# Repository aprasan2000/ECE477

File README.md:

# Purdue ECE477
Senior Design<br />
"Noggin" Smart Hard Hat<br />
BY: Akshaj Prasannakumar, Ryan Domanski, Mooyeon Kim, and Dev Shah<br />
website: https://engineering.purdue.edu/477grp19/index.html<br />
Branch with Final code is Noggin-Final Branch<br />

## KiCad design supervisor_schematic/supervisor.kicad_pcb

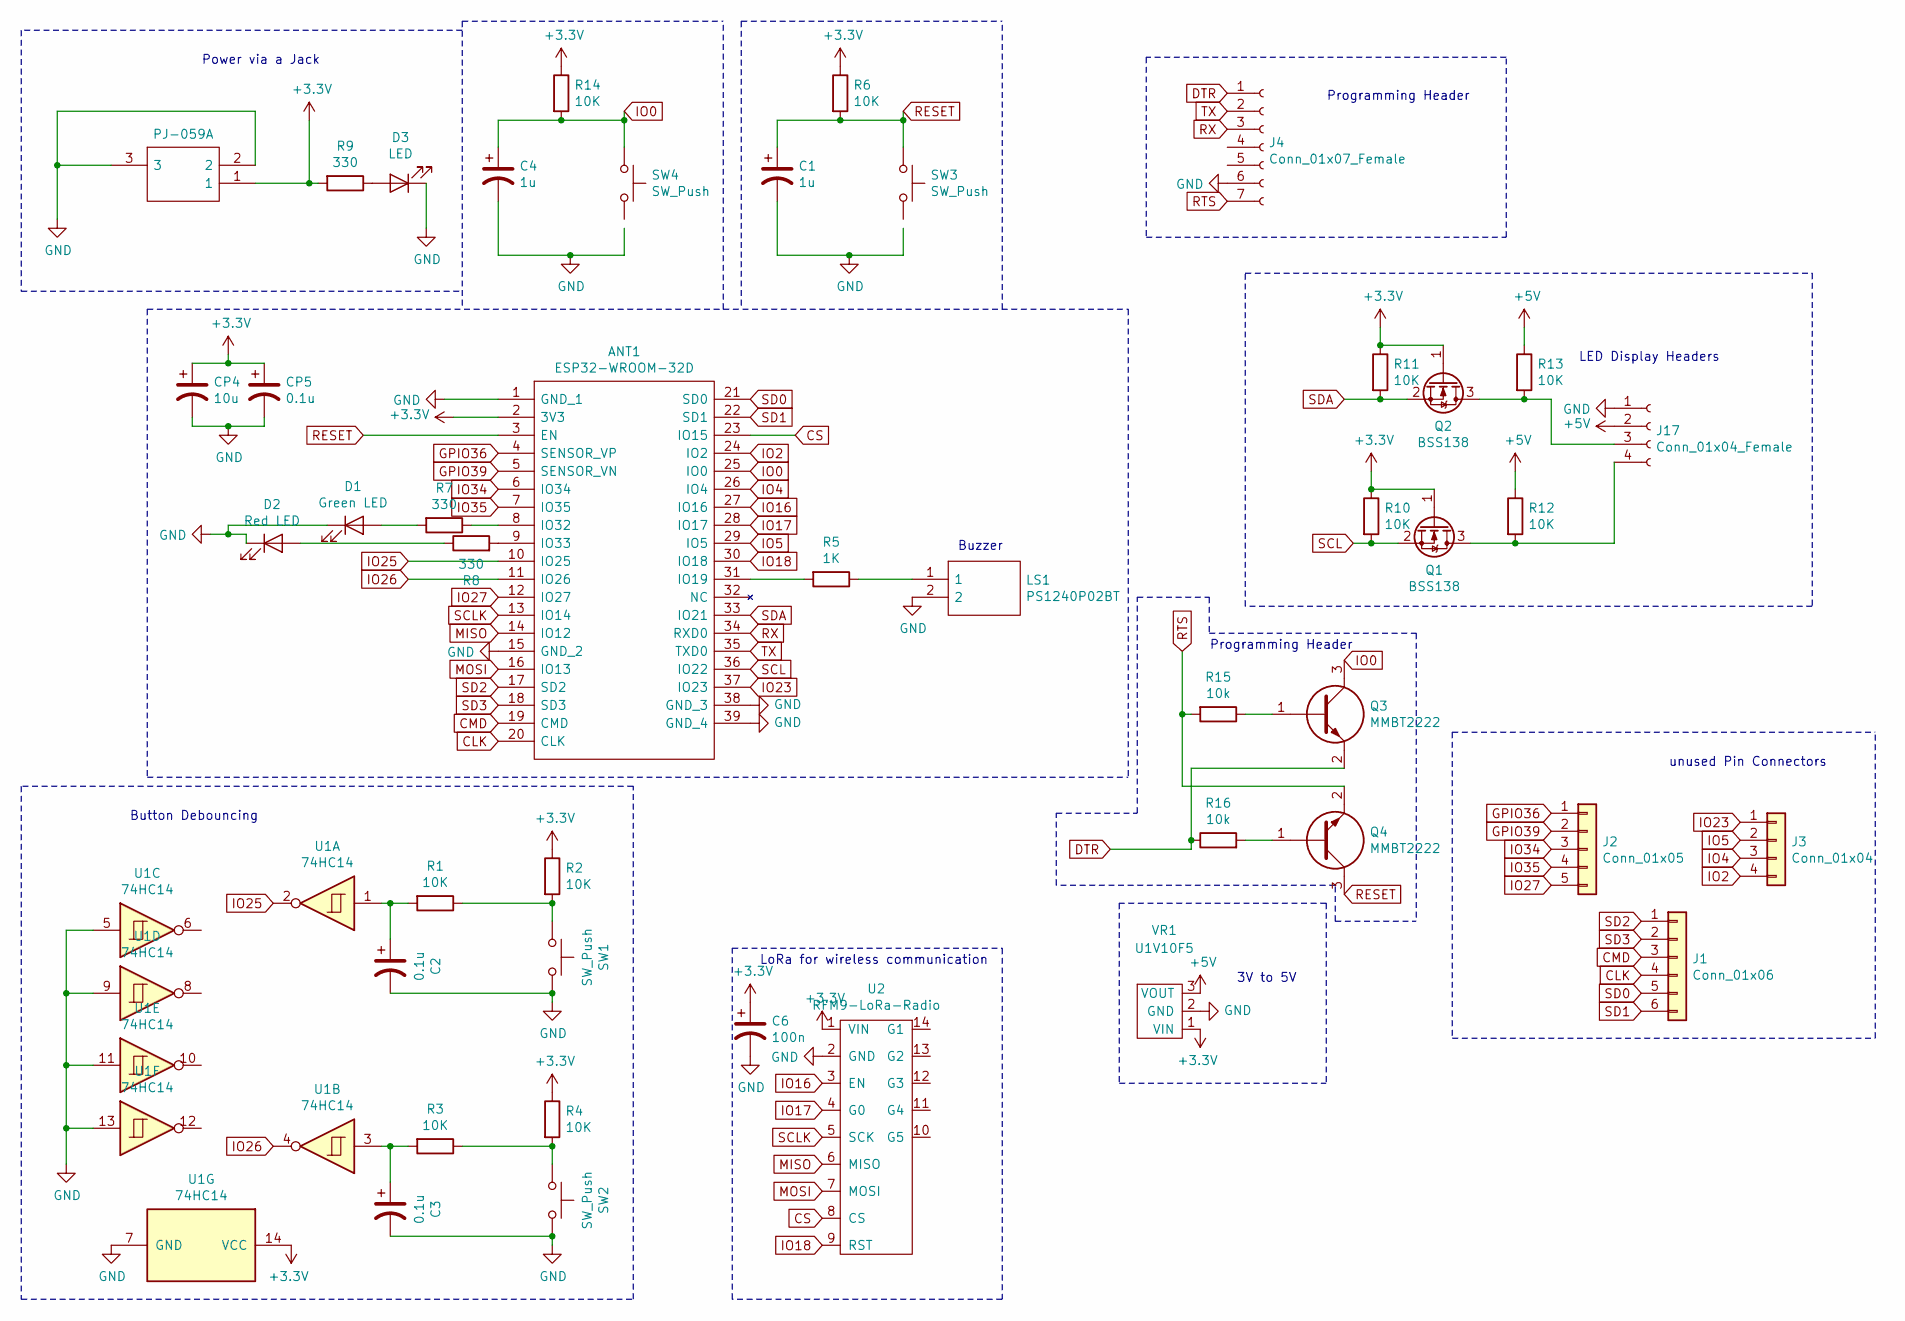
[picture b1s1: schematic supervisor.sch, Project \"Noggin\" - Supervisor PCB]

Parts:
ANT1: ESP32-WROOM-32D; ESP32WROOM32D; Manufacturer_Part_Number ESP32-WROOM-32D; Mouser Part Number N/A
C1, C4: 1u; C_0805_2012Metric_Pad1.15x1.40mm_HandSolder
C2, C3: 0.1u; C_0805_2012Metric_Pad1.15x1.40mm_HandSolder
C6: 100n; C_0805_2012Metric_Pad1.15x1.40mm_HandSolder
CP4: 10u; C_0805_2012Metric_Pad1.15x1.40mm_HandSolder
CP5: 0.1u; C_0805_2012Metric_Pad1.15x1.40mm_HandSolder
D1: Green LED; 0805_LED_Extended
D2: Red LED; 0805_LED_Extended
D3: LED; 0805_LED_Extended
J1: Conn_01x06; PinHeader_1x06_P2.54mm_Vertical
J2: Conn_01x05; PinHeader_1x05_P2.54mm_Vertical
J3: Conn_01x04; PinHeader_1x04_P2.54mm_Vertical
J4: Conn_01x07_Female; PinHeader_1x07_P2.54mm_Vertical
J17: Conn_01x04_Female; PinHeader_1x04_P2.54mm_Vertical
Jack1: PJ-059A; PJ059A; Manufacturer_Part_Number PJ-059A; Mouser Part Number 490-PJ-059A
LS1: PS1240P02BT; Manufacturer_Part_Number PS1240P02BT; Mouser Part Number 810-PS1240P02BT
Q1, Q2: BSS138; SOT-23
Q3, Q4: MMBT2222; SOT95P240X114-3N; Manufacturer_Part_Number MMBT2222; Mouser Part Number 512-MMBT2222
R1, R2, R3, R4, R6, R10, R11, R12, R13, R14: 10K; R_0805_2012Metric_Pad1.15x1.40mm_HandSolder
R5: 1K; R_0805_2012Metric_Pad1.15x1.40mm_HandSolder
R7, R8, R9: 330; R_0805_2012Metric_Pad1.15x1.40mm_HandSolder
R15, R16: 10k; R_0805_2012Metric_Pad1.15x1.40mm_HandSolder
SW1, SW2, SW3, SW4: SW_Push; SW_PUSH_6mm
U1: 74HC14; DIP-14_W7.62mm
U2: RFM9-LoRa-Radio; RFM9x
VR1: U1V10F5; U1V10F5-VR

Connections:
+3V3: ANT1.2 (3V3), C6.1, CP4.1, CP5.1, Jack1.1, Q1.1 (G), Q2.1 (G), R2.1, R4.1, R6.1, R9.2, R10.1, R11.1, R14.1, U1.14 (VCC), U2.1 (VIN), VR1.1 (VIN)
+5V: J17.2, R12.1, R13.1, VR1.3 (VOUT)
CLK: ANT1.20 (CLK), J1.4
CMD: ANT1.19 (CMD), J1.3
CS: ANT1.23 (IO15), U2.8 (CS)
DTR: J4.1, Q3.2, R16.1
GND: ANT1.1 (GND_1), ANT1.15 (GND_2), ANT1.38 (GND_3), ANT1.39 (GND_4), C1.2, C2.2, C3.2, C4.2, C6.2, CP4.2, CP5.2, D1.1 (K), D2.1 (K), D3.1 (K), J4.6, J17.1, Jack1.2, Jack1.3, LS1.2, SW1.2, SW2.2, U1.5, U1.7 (GND), U1.9, U1.11, U1.13, U2.2 (GND), VR1.2 (GND)
GPIO36: ANT1.4 (SENSOR_VP), J2.1
GPIO39: ANT1.5 (SENSOR_VN), J2.2
IO0: ANT1.25 (IO0), C4.1, Q3.3, R14.2, SW4.1
IO2: ANT1.24 (IO2), J3.4
IO4: ANT1.26 (IO4), J3.3
IO5: ANT1.29 (IO5), J3.2
IO16: ANT1.27 (IO16), U2.3 (EN)
IO17: ANT1.28 (IO17), U2.4 (G0)
IO18: ANT1.30 (IO18), U2.9 (RST)
IO23: ANT1.37 (IO23), J3.1
IO25: ANT1.10 (IO25), U1.2
IO26: ANT1.11 (IO26), U1.4
IO27: ANT1.12 (IO27), J2.5
IO34: ANT1.6 (IO34), J2.3
IO35: ANT1.7 (IO35), J2.4
MISO: ANT1.14 (IO12), U2.6 (MISO)
MOSI: ANT1.16 (IO13), U2.7 (MOSI)
unnamed: ANT1.8 (IO32), R7.1
unnamed: ANT1.9 (IO33), R8.2
unnamed: ANT1.31 (IO19), R5.2
unnamed: C2.1, R1.2, U1.1
unnamed: C3.1, R3.2, U1.3
unnamed: D1.2 (A), R7.2
unnamed: D2.2 (A), R8.1
unnamed: D3.2 (A), R9.1
unnamed: J17.3, Q2.3 (D), R13.2
unnamed: J17.4, Q1.3 (D), R12.2
unnamed: LS1.1, R5.1
unnamed: Q3.1, R15.1
unnamed: Q4.1, R16.2
unnamed: R1.1, R2.2, SW1.1
unnamed: R3.1, R4.2, SW2.1
RESET: ANT1.3 (EN), C1.1, Q4.3, R6.2, SW3.1
RTS: J4.7, Q4.2, R15.2
RX: ANT1.34 (RXD0), J4.3
SCL: ANT1.36 (IO22), Q1.2 (S), R10.2
SCLK: ANT1.13 (IO14), U2.5 (SCK)
SD0: ANT1.21 (SD0), J1.5
SD1: ANT1.22 (SD1), J1.6
SD2: ANT1.17 (SD2), J1.1
SD3: ANT1.18 (SD3), J1.2
SDA: ANT1.33 (IO21), Q2.2 (S), R11.2
TX: ANT1.35 (TXD0), J4.2

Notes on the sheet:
Power via a Jack
Button Debouncing
Programming Header
LoRa for wireless communication
unused Pin Connectors
LED Display Headers
Buzzer
3V to 5V
Programming Header

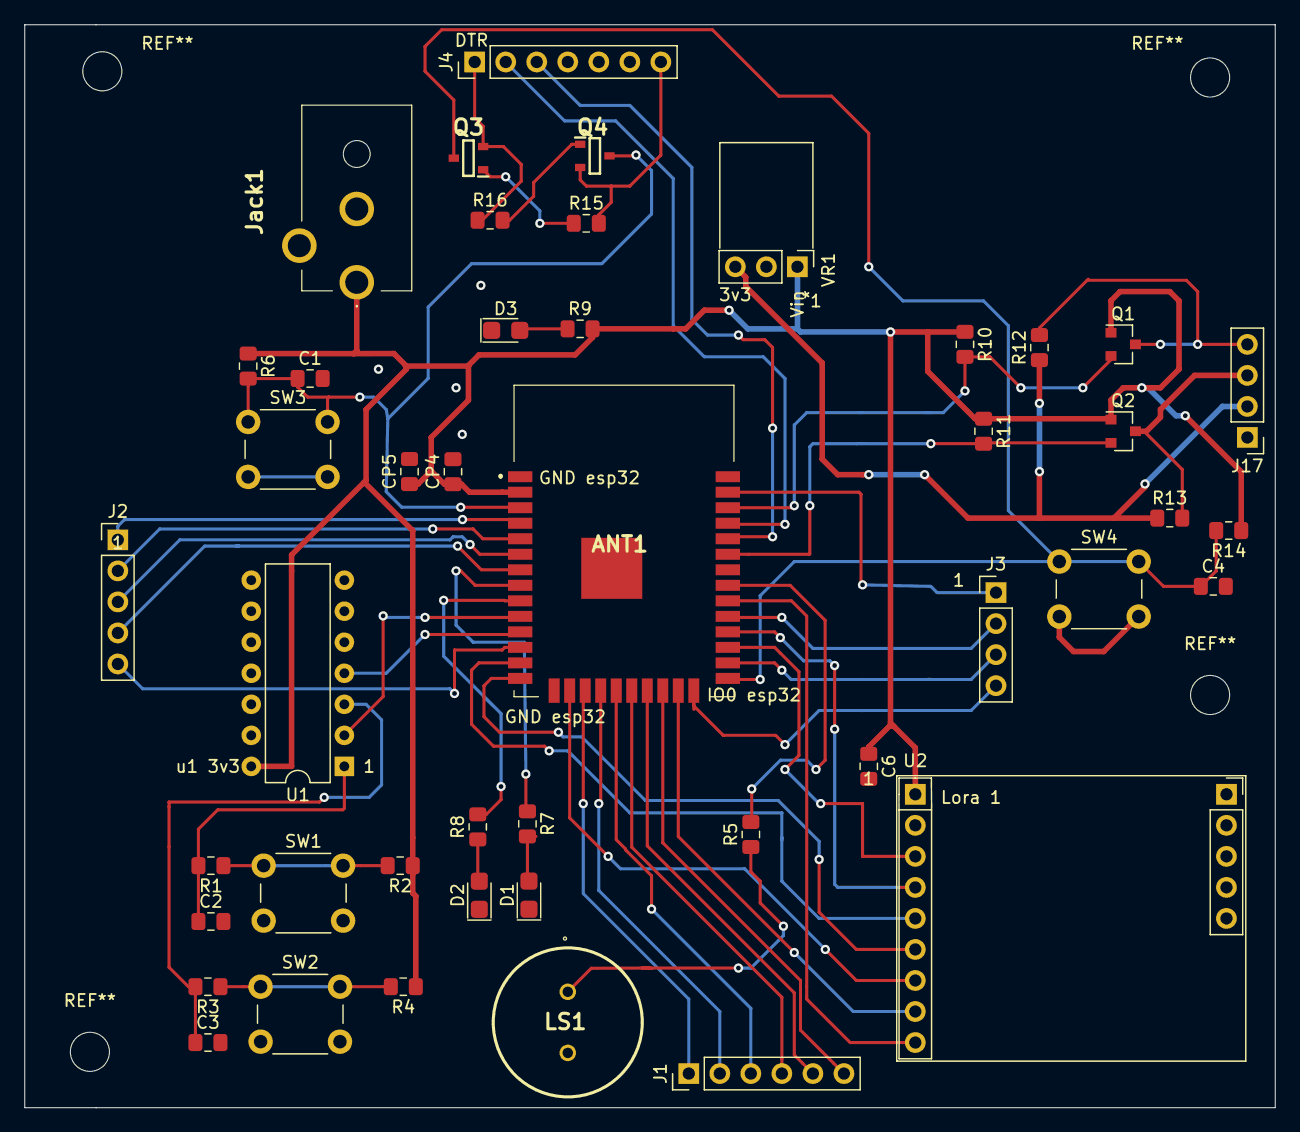
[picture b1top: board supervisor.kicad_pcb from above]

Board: 2 copper layers, 102.4 x 88.6 mm, 45 parts (0 on the bottom side), 50 nets.

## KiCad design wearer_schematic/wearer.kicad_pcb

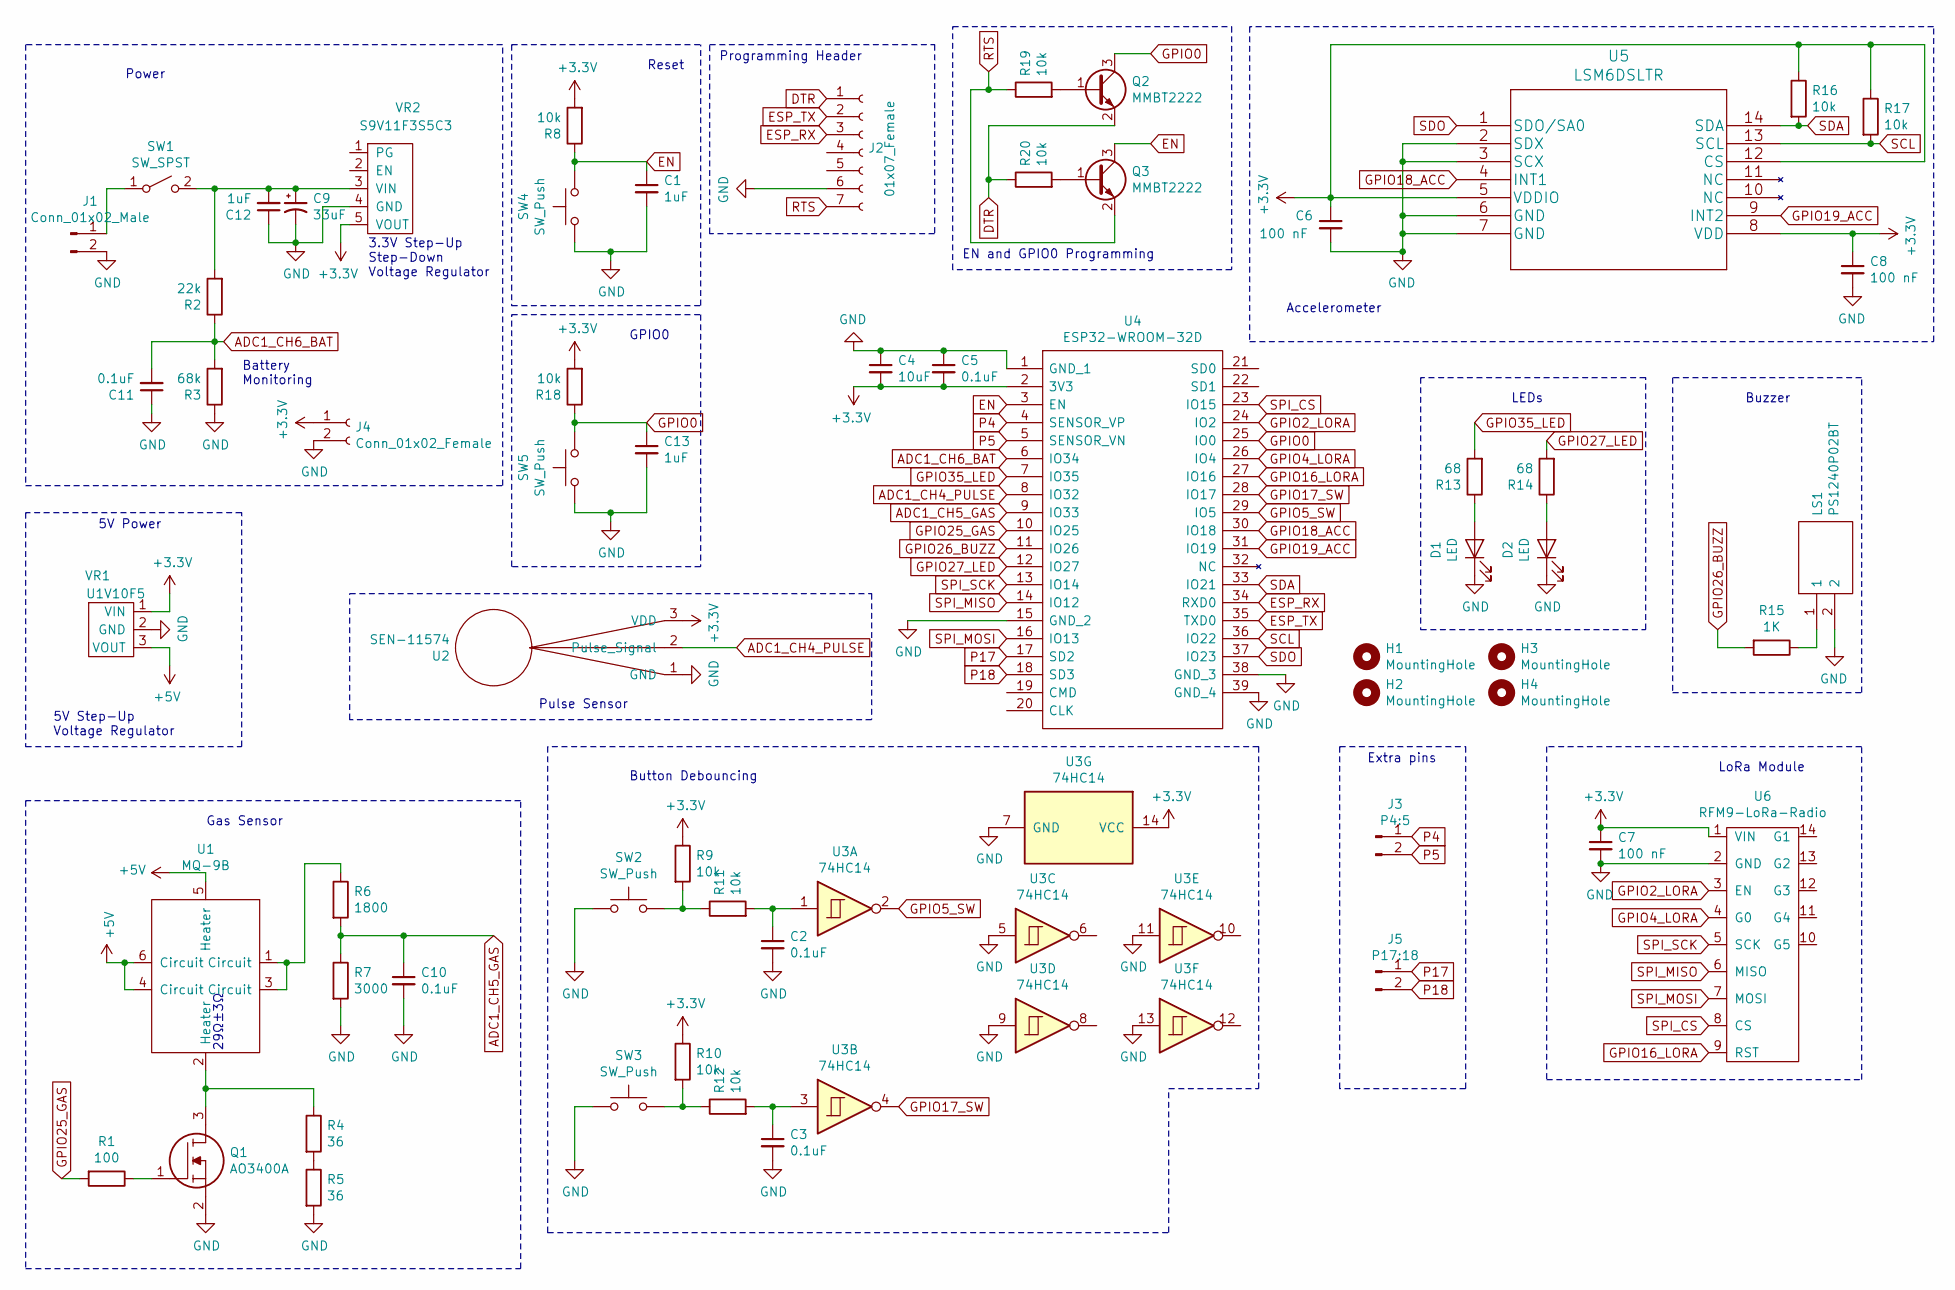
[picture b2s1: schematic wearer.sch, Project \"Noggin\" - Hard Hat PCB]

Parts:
C1, C12, C13: 1uF; C_0805_2012Metric_Pad1.15x1.40mm_HandSolder
C2, C3, C5, C10, C11: 0.1uF; C_0805_2012Metric_Pad1.15x1.40mm_HandSolder
C4: 10uF; C_0805_2012Metric_Pad1.15x1.40mm_HandSolder
C6, C7, C8: 100 nF; C_0805_2012Metric_Pad1.15x1.40mm_HandSolder
C9: 33uF; CP_Radial_D6.3mm_P2.50mm
D1, D2: LED; 0805_LED_Extended
H1, H2, H3, H4: MountingHole; MountingHole_3.2mm_M3
J1: Conn_01x02_Male; PinHeader_1x02_P2.54mm_Vertical
J2: 01x07_Female; PinSocket_1x07_P2.54mm_Vertical
J3: P4:5; PinHeader_1x02_P2.54mm_Vertical
J4: Conn_01x02_Female; PinSocket_1x02_P2.54mm_Vertical
J5: P17:18; PinHeader_1x02_P2.54mm_Vertical
LS1: PS1240P02BT; Manufacturer_Part_Number PS1240P02BT; Mouser Part Number 810-PS1240P02BT
Q1: AO3400A; SOT95P280X125-3N; Manufacturer_Part_Number AO3400A
Q2, Q3: MMBT2222
R1: 100; R_0805_2012Metric_Pad1.15x1.40mm_HandSolder
R2: 22k; R_0805_2012Metric_Pad1.15x1.40mm_HandSolder
R3: 68k; R_0805_2012Metric_Pad1.15x1.40mm_HandSolder
R4, R5: 36; R_0805_2012Metric_Pad1.15x1.40mm_HandSolder
R6: 1800; R_0805_2012Metric_Pad1.15x1.40mm_HandSolder
R7: 3000; R_0805_2012Metric_Pad1.15x1.40mm_HandSolder
R8, R9, R10, R11, R12, R16, R17, R18, R19, R20: 10k; R_0805_2012Metric_Pad1.15x1.40mm_HandSolder
R13, R14: 68; R_0805_2012Metric_Pad1.15x1.40mm_HandSolder
R15: 1K; R_0805_2012Metric_Pad1.15x1.40mm_HandSolder
SW1: SW_SPST; PinHeader_1x02_P2.54mm_Vertical
SW2, SW3: SW_Push; PinHeader_1x02_P2.54mm_Vertical
SW4, SW5: SW_Push; SW_PUSH_6mm
U1: MQ-9B
U2: SEN-11574; PinHeader_1x03_P2.54mm_Horizontal
U3: 74HC14; DIP-14_W7.62mm
U4: ESP32-WROOM-32D; ESP32WROOM32D; Manufacturer_Part_Number ESP32-WROOM-32D; Mouser Part Number N/A
U5: LSM6DSLTR
U6: RFM9-LoRa-Radio; RFM9x
VR1: U1V10F5; U1V10F5-VR
VR2: S9V11F3S5C3

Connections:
+3V3: C4.2, C5.2, C6.1, C7.1, C8.1, J4.1, R8.2, R9.1, R10.1, R16.1, R17.1, R18.2, U2.3 (VDD), U3.14 (VCC), U4.2 (3V3), U5.5 (VDDIO), U5.8 (VDD), U5.12 (CS), U6.1 (VIN), VR1.1 (VIN), VR2.5 (VOUT)
+5V: U1.4 (Circuit), U1.5 (Heater), U1.6 (Circuit), VR1.3 (VOUT)
ADC1_CH4_PULSE: U2.2 (Pulse_Signal), U4.8 (IO32)
ADC1_CH5_GAS: C10.1, R6.2, R7.1, U4.9 (IO33)
ADC1_CH6_BAT: C11.2, R2.1, R3.2, U4.6 (IO34)
DTR: J2.1, Q2.2 (E), R20.1
EN: C1.1, Q3.3 (C), R8.1, SW4.2, U4.3 (EN)
ESP_RX: J2.3, U4.34 (RXD0)
ESP_TX: J2.2, U4.35 (TXD0)
GND: C1.2, C2.2, C3.2, C4.1, C5.1, C6.2, C7.2, C8.2, C9.2, C10.2, C11.1, C12.1, C13.2, D1.1 (K), D2.1 (K), J1.2, J2.6, J4.2, LS1.2, Q1.2, R3.1, R5.2, R7.2, SW2.1, SW3.1, SW4.1, SW5.1, U2.1 (GND), U3.5, U3.7 (GND), U3.9, U3.11, U3.13, U4.1 (GND_1), U4.15 (GND_2), U4.38 (GND_3), U4.39 (GND_4), U5.2 (SDX), U5.3 (SCX), U5.6 (GND), U5.7 (GND), U6.2 (GND), VR1.2 (GND), VR2.4 (GND)
GPIO0: C13.1, Q2.3 (C), R18.1, SW5.2, U4.25 (IO0)
GPIO2_LORA: U4.24 (IO2), U6.3 (EN)
GPIO4_LORA: U4.26 (IO4), U6.4 (G0)
GPIO5_SW: U3.2, U4.29 (IO5)
GPIO16_LORA: U4.27 (IO16), U6.9 (RST)
GPIO17_SW: U3.4, U4.28 (IO17)
GPIO18_ACC: U4.30 (IO18), U5.4 (INT1)
GPIO19_ACC: U4.31 (IO19), U5.9 (INT2)
GPIO25_GAS: R1.2, U4.10 (IO25)
GPIO26_BUZZ: R15.2, U4.11 (IO26)
GPIO27_LED: R14.2, U4.12 (IO27)
GPIO35_LED: R13.2, U4.7 (IO35)
unnamed: C2.1, R11.2, U3.1
unnamed: C3.1, R12.2, U3.3
unnamed: C9.1, C12.2, R2.2, SW1.2 (B), VR2.3 (VIN)
unnamed: D1.2 (A), R13.1
unnamed: D2.2 (A), R14.1
unnamed: J1.1, SW1.1 (A)
unnamed: LS1.1, R15.1
unnamed: Q1.1, R1.1
unnamed: Q1.3, R4.1, U1.2 (Heater)
unnamed: Q2.1 (B), R19.2
unnamed: Q3.1 (B), R20.2
unnamed: R4.2, R5.1
unnamed: R6.1, U1.1 (Circuit), U1.3 (Circuit)
unnamed: R10.2, R12.1, SW3.2
unnamed: R9.2, R11.1, SW2.2
P4: J3.1, U4.4 (SENSOR_VP)
P5: J3.2, U4.5 (SENSOR_VN)
P17: J5.1, U4.17 (SD2)
P18: J5.2, U4.18 (SD3)
RTS: J2.7, Q3.2 (E), R19.1
SCL: R17.2, U4.36 (IO22), U5.13 (SCL)
SDA: R16.2, U4.33 (IO21), U5.14 (SDA)
SDO: U4.37 (IO23), U5.1 (SDO/SA0)
SPI_CS: U4.23 (IO15), U6.8 (CS)
SPI_MISO: U4.14 (IO12), U6.6 (MISO)
SPI_MOSI: U4.16 (IO13), U6.7 (MOSI)
SPI_SCK: U4.13 (IO14), U6.5 (SCK)

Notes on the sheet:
29Ω±3Ω
Gas Sensor
Button Debouncing
LoRa Module
5V Power
5V Step-Up Voltage Regulator
Pulse Sensor
Programming Header
Power
3.3V Step-Up Step-Down Voltage Regulator
Battery Monitoring
LEDs
Buzzer
Accelerometer
Extra pins
Reset
GPIO0
EN and GPIO0 Programming

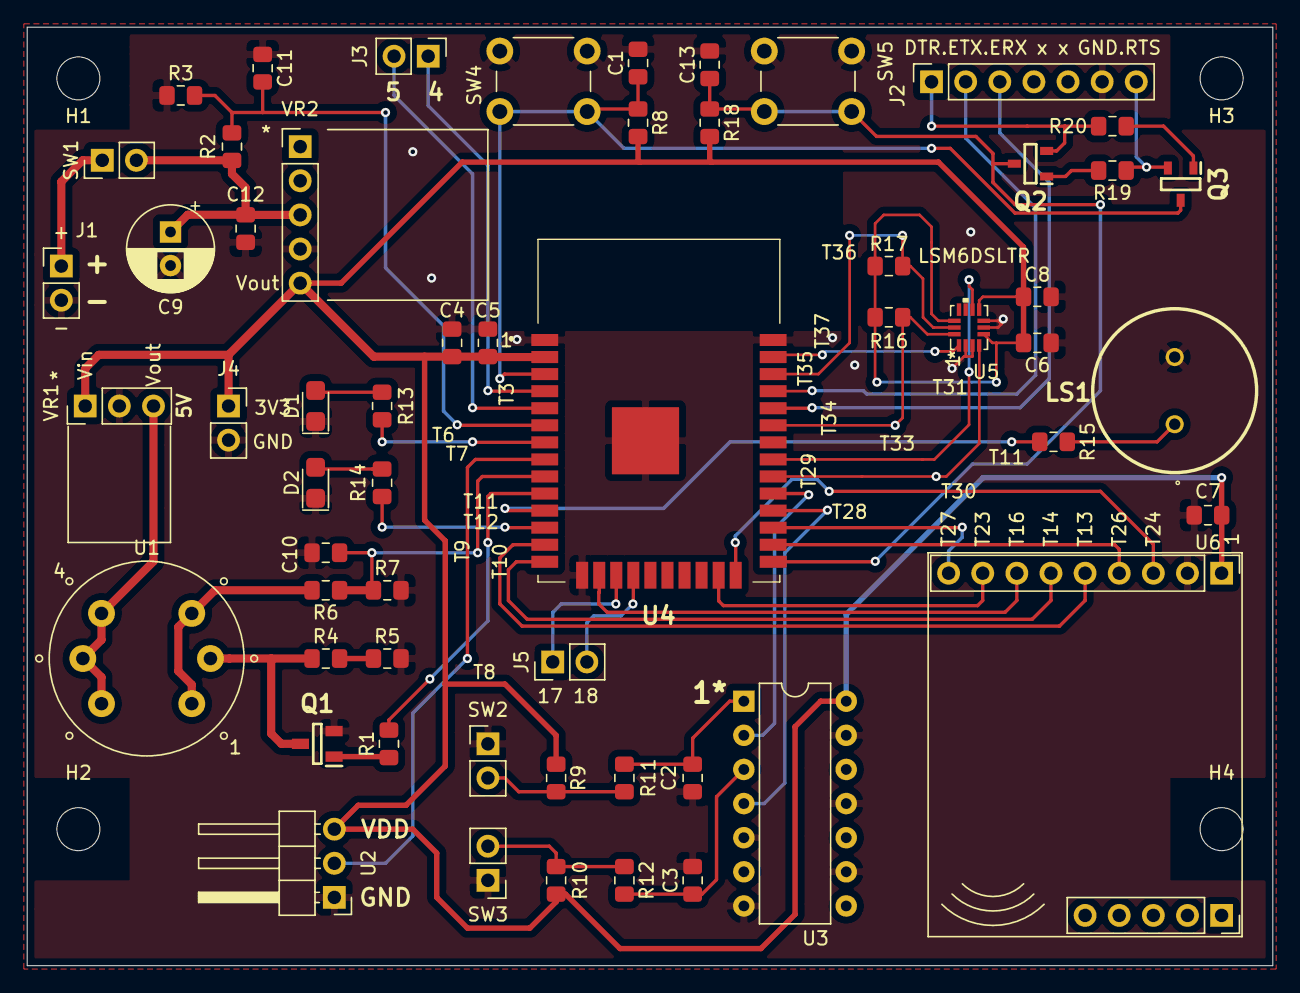
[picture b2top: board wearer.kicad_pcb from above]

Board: 2 copper layers, 92.7 x 69.8 mm, 61 parts (0 on the bottom side), 49 nets.

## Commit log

2022-02-09 Working ISR
2022-02-09 KiCad
2022-02-09 Added ADC readings
2022-02-10 Testing
    Checked if it worked on my computer
2022-02-14 Shows concurrent tasks
2022-02-14 some schem work
2022-02-14 pulse sensor analyze
2022-02-15 pulseSensorAnalyze
    pulse sensor data sent to excelsheet for analyzing.
2022-02-16 PCB started
2022-02-16 UART Example
2022-02-16 buzzer working
2022-02-20 schem work
2022-02-20 added wearer/supervisor schematic
2022-02-22 some pcb work
2022-02-23 supervisor almost done
2022-02-23 Create acc.c
    ignore wifi part for now
2022-02-24 button debouncing schem
2022-02-25 supervisor schem work
2022-02-26 added to schematic
2022-02-27 more supervisor schem work
2022-02-27 updated wearer schematic
2022-02-28 update schematic
2022-02-28 update debouncing
2022-02-28 add espflasher
2022-02-28 update shematic
2022-02-28 schem v1 done
2022-02-28 add decoupling caps to esp
2022-03-01 added footprints
2022-03-01 added esp footprint
2022-03-02 started footprint
2022-03-02 Add files via upload
    ignore the previous header file
2022-03-02 going to layout supervisor
2022-03-03 edit pcb
2022-03-03 Create LoRa_receiver
2022-03-03 ratsnest supervisor
2022-03-03 arranging components
2022-03-03 before adding decoupling to power
2022-03-03 everything but ground plane
2022-03-03 ground planes
2022-03-03 pcb cleanup
2022-03-03 started routing
2022-03-04 supervisor done
2022-03-09 update pcb
2022-03-09 schematic v1
2022-03-10 v2 almost done
2022-03-10 progress
2022-03-11 before order
2022-03-11 ordered
2022-03-11 pcb finished
2022-03-24 supervisor schem
2022-04-04 added git ignore
2022-04-04 pssc testing
2022-04-04 gitignore
2022-04-04 pwm progress
2022-04-05 gas sensor prelim working
2022-04-06 some pcb supervisor changes
2022-04-12 Create LoRa_receiver_final
2022-04-12 Supervisor_buzzer
    pin changed(sup)
2022-04-12 Rename LoRa_receiver_final to LoRa_receiver_final.c
2022-04-13 Create Noggin_wearer
    Just LoRa function for now
2022-04-13 Create Noggin_super
    Just LoRa function for now
2022-04-13 Rename Noggin_wearer to Noggin_wearer.c
2022-04-13 Rename Noggin_super to Noggin_super.c
2022-04-17 pulse sensor reading
    Pulse sensor is reading data from the actual pcb board on the ear lobe. need to do some threshold setting and actual alerting
2022-04-19 Accel, Battery, and Pulse
2022-04-20 Accel header file
    Add file to ~/esp-idf/components/driver/include/driver
2022-04-20 gas sensor
2022-04-20 3 processing running at once
2022-04-20 gas sensor heat up
2022-04-20 Update LoRa_receiver_final.c
    pin changed
2022-04-20 LoRa working
2022-04-21 button isr
2022-04-21 Mostly working
2022-04-21 new pulse
2022-04-22 Final code
